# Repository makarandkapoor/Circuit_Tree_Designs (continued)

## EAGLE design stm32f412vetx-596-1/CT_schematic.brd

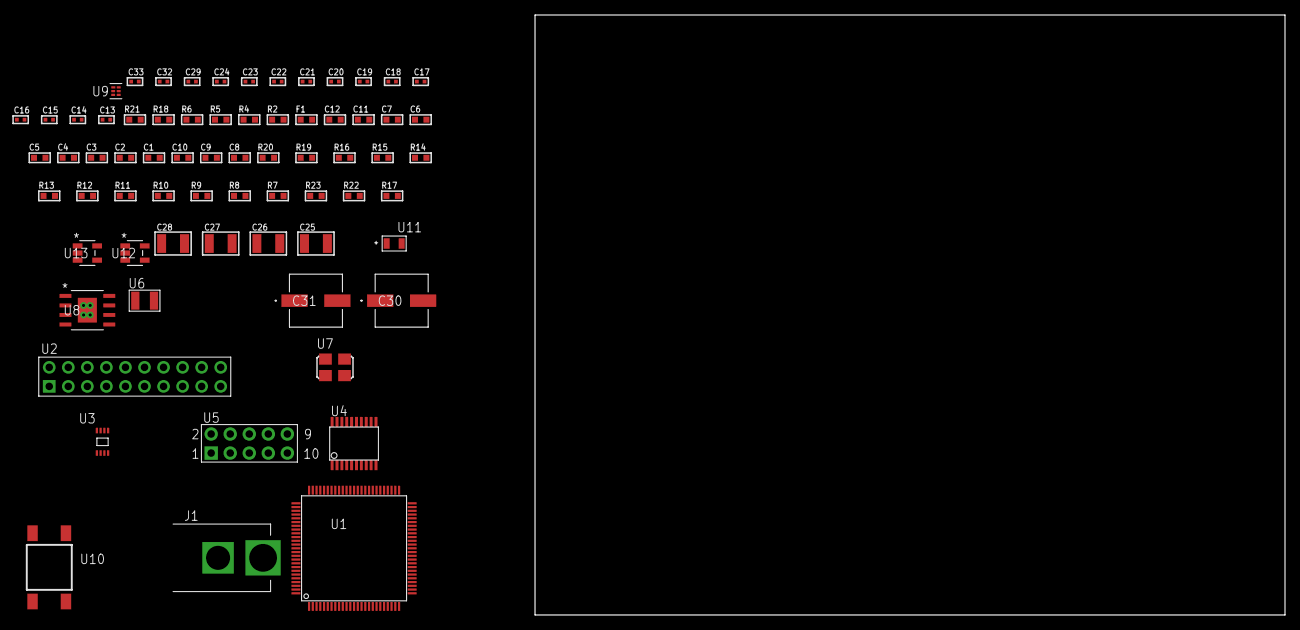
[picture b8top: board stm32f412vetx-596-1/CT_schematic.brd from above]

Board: 2 copper layers, 100.0 x 80.0 mm, 69 parts (0 on the bottom side), 43 nets, no tracks yet.

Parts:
C1, C12: 1e-06; C0603
C2, C3, C4, C5, C6, C7: 1e-07; C0603
C8: 4.7e-06; C0603
C9, C10: 2.2e-06; C0603
C11: 1e-08; C0603
C13, C14: 1e-11; C0402
C15, C16, C18, C19, C20, C21, C22, C23, C29: 1e-07; C0402
C17, C24, C32, C33: 1e-08; C0402
C25, C26, C27, C28: 1e-05; C1210
C30, C31: 0.0001; EXV-9H
F1: 240.0; L0603
J1: PJ-037B; PJ-037B_PACKAGE
R2: 1000.0; R0603
R4: 4700.0; R0603
R5, R6, R18: 2200.0; R0603
R7, R8, R9, R10, R11, R12, R13, R14, R15, R16, R19, R20: 10000.0; R0603
R17: 4031.5447154472; R0603
R21: 9100.0; R0603
R22: 680000.0; R0603
R23: 120000.0; R0603
U1: STM32F412VET6; LQFP100
U2: TST-110-05-T-D-RA
U3: 24AA32AT-I/MNY; TDFN-8/6MM
U4: SP3203ECY-L/TR; TSSOP20-I
U5: HTSS-105-01-G-D
U6: ABS07-32.768KHZ-7-T
U7: ASFL1-25MHZ-NCS; ASFL1
U8: MIC5234YME; SOIC-8_EP
U9: TPS3895ADRYR; SON-6
U10: 4-1437565-2; SW_4-1437565-2
U11: Q65110A2395; LGM67K-G1J2-24-Z
U12, U13: nc7sz125m5x; NC7SZ125M5X

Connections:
CLK_CRYSTAL_U1_8: C13.1, U1.8, U6.1
CLK_CRYSTAL_U1_9: C14.1, U1.9, U6.2
CLK_U1_12: U1.12, U7.3
GND: C1.2, C2.2, C3.2, C4.2, C5.2, C6.2, C7.2, C8.2, C9.2, C10.2, C11.2, C12.2, C13.2, C14.2, C15.2, C16.2, C17.2, C18.2, C19.2, C22.2, C23.2, C24.2, C25.2, C26.2, C27.2, C28.2, C29.2, C30.2, C31.2, C32.2, C33.2, J1.2, R2.2, R7.2, R13.2, R18.2, R21.2, R23.2, U1.10, U1.20, U1.27, U1.49, U1.74, U1.99, U2.4, U2.6, U2.8, U2.10, U2.12, U2.14, U2.16, U2.18, U2.20, U3.4, U3.7, U4.18, U5.9, U7.2, U8.7, U8.EPAD, U9.2, U11.C, U12.2, U12.3, U13.1, U13.3
NET_U1_14: R4.1, U1.14, U13.4
NET_U1_22: C11.1, C12.1, F1.1, U1.21, U1.22
NET_U1_48: C9.1, U1.48
NET_U1_73: C10.1, U1.73
NET_U1_92: R5.1, U1.92, U3.6
NET_U1_93: R6.1, U1.93, U3.5
NET_U1_94: R7.1, U1.94
NET_U1_98: U10.3, U10.4
NET_U2_19: R13.1, U2.19
NET_U3_1: R14.1, U3.1
NET_U3_2: R15.1, U3.2
NET_U3_3: R16.1, U3.3
NET_U4_1: C20.1, U4.1
NET_U4_2: C22.1, U4.2
NET_U4_3: C20.2, U4.3
NET_U4_4: C21.1, U4.4
NET_U4_5: C21.2, U4.5
NET_U4_6: C23.1, U4.6
NET_U5_3: U4.14, U5.3
NET_U5_4: U4.13, U5.4
NET_U5_5: U4.17, U5.5
NET_U5_6: U4.16, U5.6
NET_U8_4: R17.2, R18.1, U8.4
NET_U9_1: R20.1, R21.1, U9.1
NET_U9_3: R22.2, R23.1, U9.3
NET_U9_4: R19.1, U9.4, U12.4, U13.2
NET_U10_1: R2.1, U10.1, U10.2
PROC_SYS_JTCK_SWCLK: R11.1, U1.76, U2.9
PROC_SYS_JTDI: R9.1, U1.77, U2.5
PROC_SYS_JTDO_SWO: U1.89, U2.13
PROC_SYS_JTMS_SWDIO: R10.1, U1.72, U2.7
PROC_SYS_JTRST: R8.1, U1.90, U2.3
PROC_USART1_CTS: U1.70, U4.8
PROC_USART1_RTS: U1.71, U4.10
PROC_USART1_RX: U1.69, U4.11
PROC_USART1_TX: U1.68, U4.7
RST_OUT_U2_SRESET_B: R12.1, U2.15, U12.1
VCC_S1_7V7: C25.1, C26.1, C30.1, C31.1, J1.1, U8.5, U8.8
VCC_TIER1_3V3: C1.1, C2.1, C3.1, C4.1, C5.1, C6.1, C7.1, C8.1, C15.1, C16.1, C17.1, C18.1, C19.1, C24.1, C27.1, C28.1, C29.1, C32.1, C33.1, F1.2, R4.2, R5.2, R6.2, R8.2, R9.2, R10.2, R11.2, R12.2, R14.2, R15.2, R16.2, R17.1, R19.2, R20.2, R22.1, U1.6, U1.11, U1.19, U1.28, U1.50, U1.75, U1.100, U2.1, U2.2, U3.8, U4.12, U4.19, U7.4, U8.1, U9.6, U12.5, U13.5
